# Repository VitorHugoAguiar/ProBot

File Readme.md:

# ProBot - The Self Balancing Protest Robot

> “…Our leading bankers and merchants speak to their congeners through the length and breadth of the land in a second of time; their rich and subtle souls can defy all material impediment, whereas the souls of the poor are clogged and hampered by matter, which sticks fast about them as treacle to the wings of a fly, or as one struggling in a quicksand: their dull ears must take days or weeks to hear what another would tell them from a distance, instead of hearing it in a second as is done by the more highly organised classes.  Who shall deny that one who can tack on a special train to his identity, and go wheresoever he will whensoever he pleases, is more highly organised than he who, should he wish for the same power, might wish for the wings of a bird with an equal chance of getting them; and whose legs are his only means of locomotion?  That old philosophic enemy, matter, the inherently and essentially evil, still hangs about the neck of the poor and strangles him: but to the rich, matter is immaterial; the elaborate organisation of his extra-corporeal system has freed his soul.” 
> -Samuel Butler, [Erewhon, Book of the Machines](https://www.gutenberg.org/files/1906/1906-h/1906-h.htm), 1872

Most robotics technologies are first implemented in military applications, most of the rest for business. Following on a history of related work, Probots are inexpensive, human-sized protest robots. No one has lost money by replacing human labor with machines, efficient devils, so the unemployment has been rising, and newly graduated Spanish students that are out of work stay too much time drinking calimocho and protesting. The indignados are unorganized and inneficient! So it is time to automate them, send robots for protests, unemploying them twice.
	
Any protester can control the robot while sitting in the caffee or at their gardens anywhere in the work by simply using a web page to control it, but also watch, hear and speak through it.
	
That’s why we created a self-balancing robot, with a rigid sturdy frame, a megaphone on the top as a symbol of protest and also as a way to talk to people.
	
This robot is 1,60m (5’/3’’) tall that self-balances in 2 wheels, controlled by a Sabertooth 2X25A or Cytron 13A 5-25V Motor Controller. The brain of the operation is a Beaglebone Black with an MPU6050 accelerometer and gyroscope and also optical encoders on each motor.
	
A shield was created to organize the components. The system is power-up by a 24V battery.
	
The megaphone is a DH-12, that has a siren and a microphone, that we hacked and placed a wire to connect to a sound jack output, enabling us to connect the megaphone to almost any device (ex: smartphone, MP3 player, laptop, you name it).
	
The system can be controlled remotely through wifi, using a smartphone hotspot connected to 3G or 4G network. A web page was created with the possibility of viewing the status of the probot, where if available can be controlled. Each ProBot can be controled with a touch device (a smartphone or a tablet), with a gamepad or even with the keyboard.

Any person can build a ProBot by just following the instructions available on [instructubles](http://www.instructables.com/id/ProBot-the-Protesting-Robot/). Thanks to Julio Fernandez Ostolaza, and la fabrica de las cosas bonitas for the inspiration.

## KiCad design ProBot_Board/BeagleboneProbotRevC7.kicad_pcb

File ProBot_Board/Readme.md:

# Probot Board

Greetings, this version of the board is an evolution from what we already have, if you find any problem, please report.
The board have an input for 5V in the top (Ethernet port side) to power the board and a 24V input to monitor the battery voltage (Don't put higher than this voltage or youll burn the microcontroller or the ADC).

To control, we have two PWM ouputs one for each controller if used the same as us and an output for the Sabertooth 2X25A.

There are also two inputs for the encoders with the usual order A, Vcc, B, empty, Gnd. You need to have atention on wich you connect to that the robot doesn't go in the wrong way.

This shield is ready to put the MPU6050 acelerometer.

For future work, we are thinking to incorporate a LiPo battery monitor with the TI BQ76930 and BQ78350 devices, and change it all to SMD circuit, integrating the MPU6050.

Here is a table with the gpio's used on this shield.

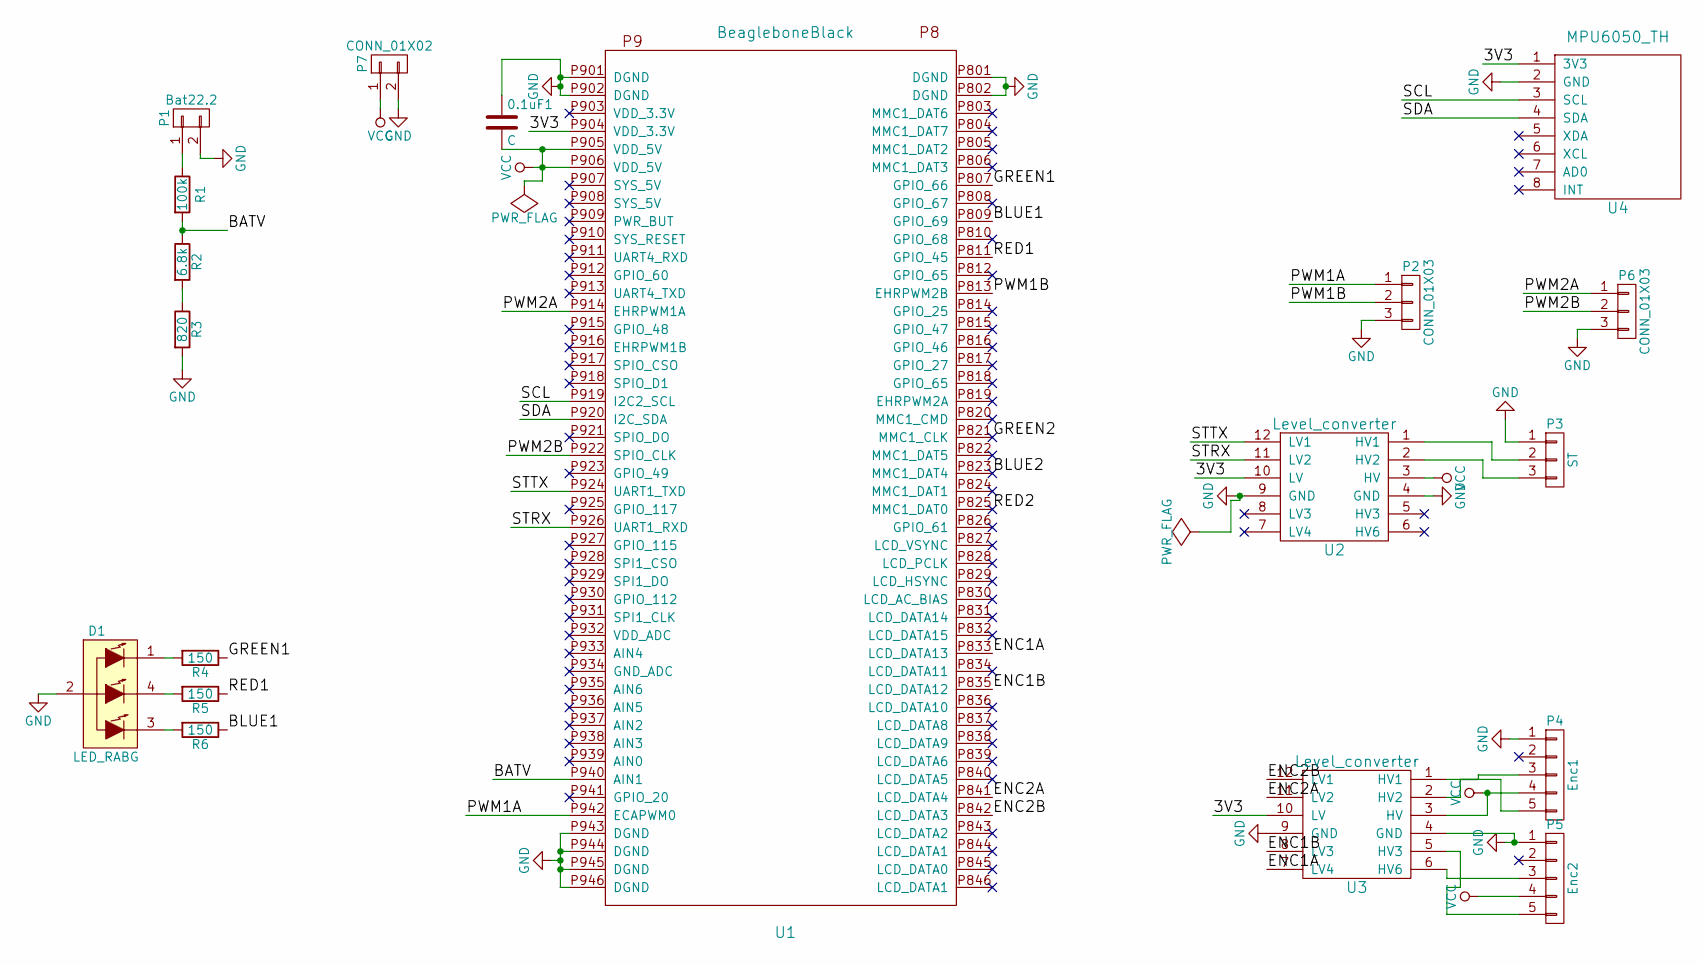
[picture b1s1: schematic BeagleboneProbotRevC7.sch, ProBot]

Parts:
0.1uF1: C; C_Disc_D3_P2.5
D1: LED_RABG; LED_RGB_common_cathode5mm
P1: Bat22.2; Pin_Header_Straight_1x02
P2, P6: CONN_01X03; Socket_Strip_Angled_1x03
P3: ST; Pin_Header_Straight_1x03
P4: Enc1; Pin_Header_Straight_1x05
P5: Enc2; Pin_Header_Straight_1x05
P7: CONN_01X02; Socket_Strip_Straight_1x02
R1: 100k; Resistor_Horizontal_RM10mm
R2: 6.8k; Resistor_Horizontal_RM10mm
R3: 820; Resistor_Horizontal_RM10mm
R4, R5, R6: 150; Resistor_Horizontal_RM10mm
U1: BeagleboneBlack; BeaglecapePro_foot
U2, U3: Level_converter; Level_Converter
U4: MPU6050_TH; Pin_Header_Straight_1x08

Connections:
/3V3: U1.P904 (VDD_3.3V), U2.10 (LV), U3.10 (LV), U4.1 (3V3)
/BATV: R1.2, R2.1, U1.P940 (AIN1)
/BLUE1: R6.1, U1.P809 (GPIO_69)
/BLUE2: U1.P823 (MMC1_DAT4)
/ENC1A: U1.P833 (LCD_DATA13), U3.7 (LV4)
/ENC1B: U1.P835 (LCD_DATA12), U3.8 (LV3)
/ENC2A: U1.P841 (LCD_DATA4), U3.11 (LV2)
/ENC2B: U1.P842 (LCD_DATA3), U3.12 (LV1)
/GREEN1: R4.1, U1.P807 (GPIO_66)
/GREEN2: U1.P821 (MMC1_CLK)
/PWM1A: P2.1, U1.P942 (ECAPWM0)
/PWM1B: P2.2, U1.P813 (EHRPWM2B)
/PWM2A: P6.1, U1.P914 (EHRPWM1A)
/PWM2B: P6.2, U1.P922 (SPIO_CLK)
/RED1: R5.1, U1.P811 (GPIO_45)
/RED2: U1.P825 (MMC1_DAT0)
/SCL: U1.P919 (I2C2_SCL), U4.3 (SCL)
/SDA: U1.P920 (I2C_SDA), U4.4 (SDA)
/STRX: U1.P926 (UART1_RXD), U2.11 (LV2)
/STTX: U1.P924 (UART1_TXD), U2.12 (LV1)
GND: 0.1uF1.1, D1.2 (COMMON_ANODE), P1.2, P2.3, P3.1, P4.1, P5.1, P6.3, P7.2, R3.2, U1.P801 (DGND), U1.P802 (DGND), U1.P901 (DGND), U1.P902 (DGND), U1.P943 (DGND), U1.P944 (DGND), U1.P945 (DGND), U1.P946 (DGND), U2.4 (GND), U2.9 (GND), U3.4 (GND), U3.9 (GND), U4.2 (GND)
unnamed: D1.1 (RED_CATHODE), R4.2
unnamed: D1.3 (BLUE_CATHODE), R6.2
unnamed: D1.4 (GREEN_CATHODE), R5.2
unnamed: P1.1, R1.1
unnamed: P3.2, U2.1 (HV1)
unnamed: P3.3, U2.2 (HV2)
unnamed: P4.3, U3.2 (HV2)
unnamed: P4.5, U3.1 (HV1)
unnamed: P5.3, U3.6 (HV6)
unnamed: P5.5, U3.5 (HV3)
unnamed: R2.2, R3.1
VCC: 0.1uF1.2, P4.4, P5.4, P7.1, U1.P905 (VDD_5V), U1.P906 (VDD_5V), U2.3 (HV), U3.3 (HV)

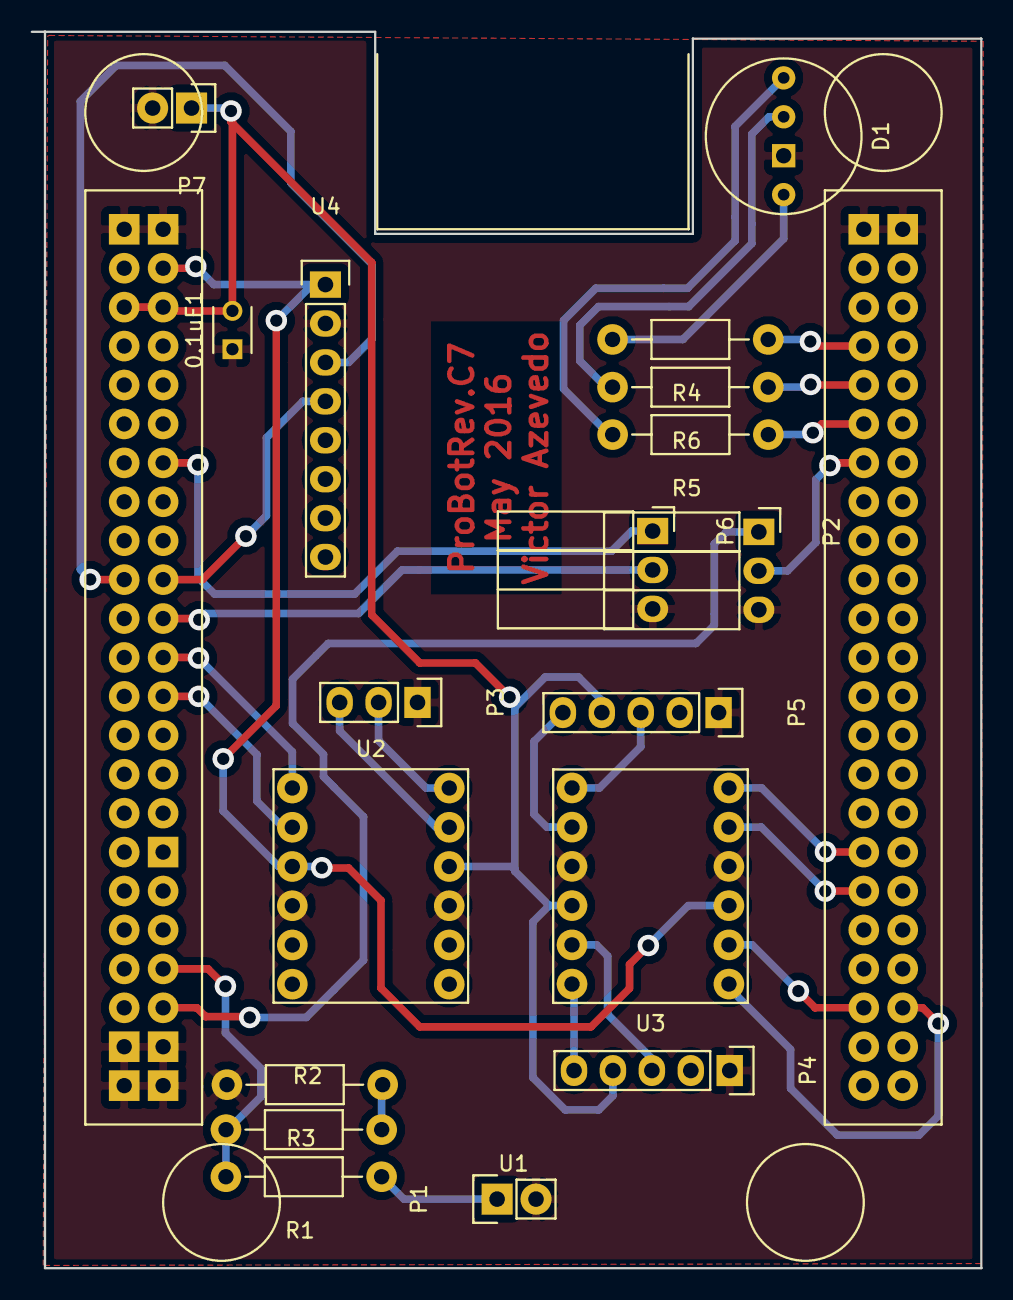
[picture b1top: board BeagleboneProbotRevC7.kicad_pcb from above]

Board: 2 copper layers, 62.0 x 80.7 mm, 19 parts (0 on the bottom side), 30 nets.

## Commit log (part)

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2016-05-20 deleted the ProBot_Desktop because we know can control the ProBot's with the joystick frm the webpage
2016-05-20 change the webserver.Now the filter is applied on the ProBot_Beaglebone
2016-05-20 Now the LowFilter is applied on the ProBot.
2016-06-02 Removed the network-manager 1.0.4
2016-06-02 just a update
2016-06-08 Removed the midi uc33 and the restart program
2016-06-16 shutdown after install everything
2016-06-21 changed the communication bettween the webpage and the Probot, using now 4 variables
2016-06-29 add battery voltage to the web interface
2016-06-29 litle change on the code structure
2016-06-30 changed the index.html
2016-06-30 changed the webserver
2016-06-30 litle change on webserver
2016-06-30 add ProBot Board
2016-06-30 ProBot shield for Sabertooth and PWM controllers
2016-06-30 Update and rename Untitled Document to Board information
    Adding information
2016-06-30 changed the velocity controller to position Controller
2016-06-30 Update Board information
2016-06-30 Rename Board information to Readme.md
2016-06-30 Update Readme.md
    update readme from boards
2016-06-30 change the velocity to position controller
2016-07-06 change the organization of the algorithm, putting several functions on diferents files
2016-07-12 add the possibility to install the necessary stuff on the beaglebone using salt
2016-07-12 minor update
2016-07-14 update index2 e ind
2016-07-14 update dist
2016-07-18 shutdown more smooth
2016-07-19 change the way of the crossbar installion
2016-07-19 minor change
2016-07-19 add salt-minion
2016-07-20 chnge the ofdet angle
2016-08-05 change to the crossbar.io WAMP
2016-08-11 just an update
2016-08-30 2 topics for each probot
2016-08-31 change the installion script
2016-09-17 after the implementaion of the flaskstarter webpage
2016-09-17 add flask-started
2016-09-17 Change readme an add Probot_server
2016-09-17 change the readme
2016-09-19 change the index
2016-09-19 change the readme and the contributors
2016-09-26 changed the text, we already tested the board and it's working properly
2016-10-19 fixed the function battery_timeout
2016-10-24 change setup.sh
2016-10-24 changed the setup.py
2016-10-25 change ProBot Board readme
2016-11-10 chnge web interface
2016-11-10 change the interface and some timers
2016-11-22 mininal improvements
2016-11-28 update from beagle
2016-11-28 change the mpu6050 file
2016-11-28 change the template for the webpage
2016-11-30 fixed the websocket
2016-11-30 fixed websocket on the flaskstarted
2016-11-30 fixed websockets
2016-12-05 improvements on the code structure
2017-01-05 changed the website and the way of sending the battery value
2017-01-05 minor changes
2017-01-05 changed the setup file
2017-01-05 remove *.pyc files
2017-01-05 changed the restart function
2017-01-05 minor changes on Probot.py
2017-01-05 remove *.pyc
2017-01-05 change restart function on pwm e saber files
2017-01-16 changed webclient
2017-01-17 update webclient
2017-01-17 wiskas
2017-02-08 Add the possibility to send angle to the server
2017-03-09 ProBot final version 1.0
2017-03-13 Minor updates
2017-03-13 update PID (position) values
2017-03-13 crossbar and flask carnival version
2017-03-16 change restartfile and pid values
2017-03-23 Probot 1
2017-03-27 ProBot 1.1
2017-03-31 fixed the position controller to velocity controller
2017-04-04 change the PID values
2017-04-19 add a possibility to start and stop the main script from the webpage
2017-04-19 changed the webpage to be a able to start and stop the main routine
2017-04-21 improve probot_admin
2017-04-21 update angle and startandstop
2017-04-24 improve adc readings
2017-04-24 change the battery zones
2017-04-26 improve startandstop from webpage
2017-05-03 improve StartAndStop from web
2017-05-23 minor update website
2017-08-17 add mqtt
2017-08-17 Revert "add mqtt"
    This reverts commit dc8f5484f01bab22b82e783d176039f1acbab861.
2017-08-17 change the communication between server and beaglebone to mqtt
2017-08-17 images readme
2017-08-17 ProBot_BeagleBone readme
2017-08-17 added gallery videos
2017-08-17 changed the communication between server and probot to mqtt protocol
2017-08-17 changed readme
2017-08-17 changed the probots images
2017-08-17 add interface image
2017-08-18 fix more than one probot available
2017-11-16 fix controller choose error and removed the videos
2017-12-29 add youtube videos and small changes
2018-01-02 remove horizontal sidebar
2018-01-26 improve user control
2018-01-26 Revert "improve user control"
    This reverts commit 74c97290af92022db149f49e8890ba9d7dffe153.
2018-01-29 change setup
2018-01-31 updated pid values and control values
2018-03-12 code cleanup and improved some files
2018-03-16 fix login/logout
2018-09-06 change website layout
2018-09-06 change database
2018-09-20 change admin page
2018-09-26 last version ProBot Code
2018-09-28 last version website
2018-09-28 indentation
